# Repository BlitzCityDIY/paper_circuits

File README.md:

# paper_circuits
Repo for files used to create paper circuits with the Cricut

Cricut project link: https://design.cricut.com/landing/project-detail/5ef37191eb1aa703a4060cc2

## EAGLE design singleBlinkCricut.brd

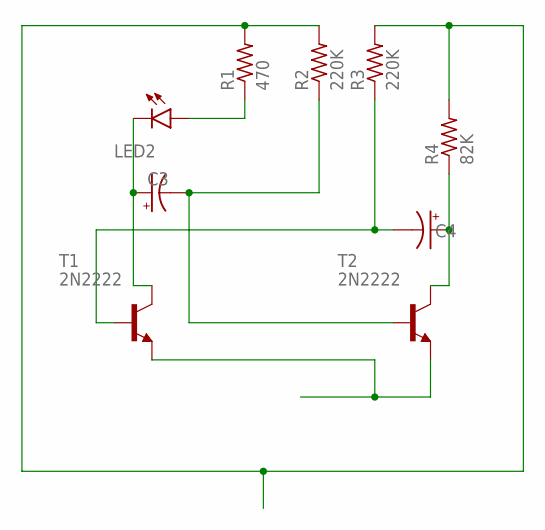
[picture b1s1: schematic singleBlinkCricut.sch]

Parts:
C3, C4: CPOL-USE2.5-6; E2,5-6
LED2: LED10MM
R1: 470; 0411/12
R2, R3: 220K; 0411/12
R4: 82K; 0411/12
T1, T2: 2N2222; TO92-EBC-OVAL

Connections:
3V: R1.2, R2.2, R3.2, R4.2
GND: T1.E, T2.E
unnamed: C3.-, R2.1, T2.B
unnamed: C3.+, LED2.K (C), T1.C
unnamed: LED2.A, R1.1
unnamed: C4.-, R3.1, T1.B
unnamed: C4.+, R4.1, T2.C

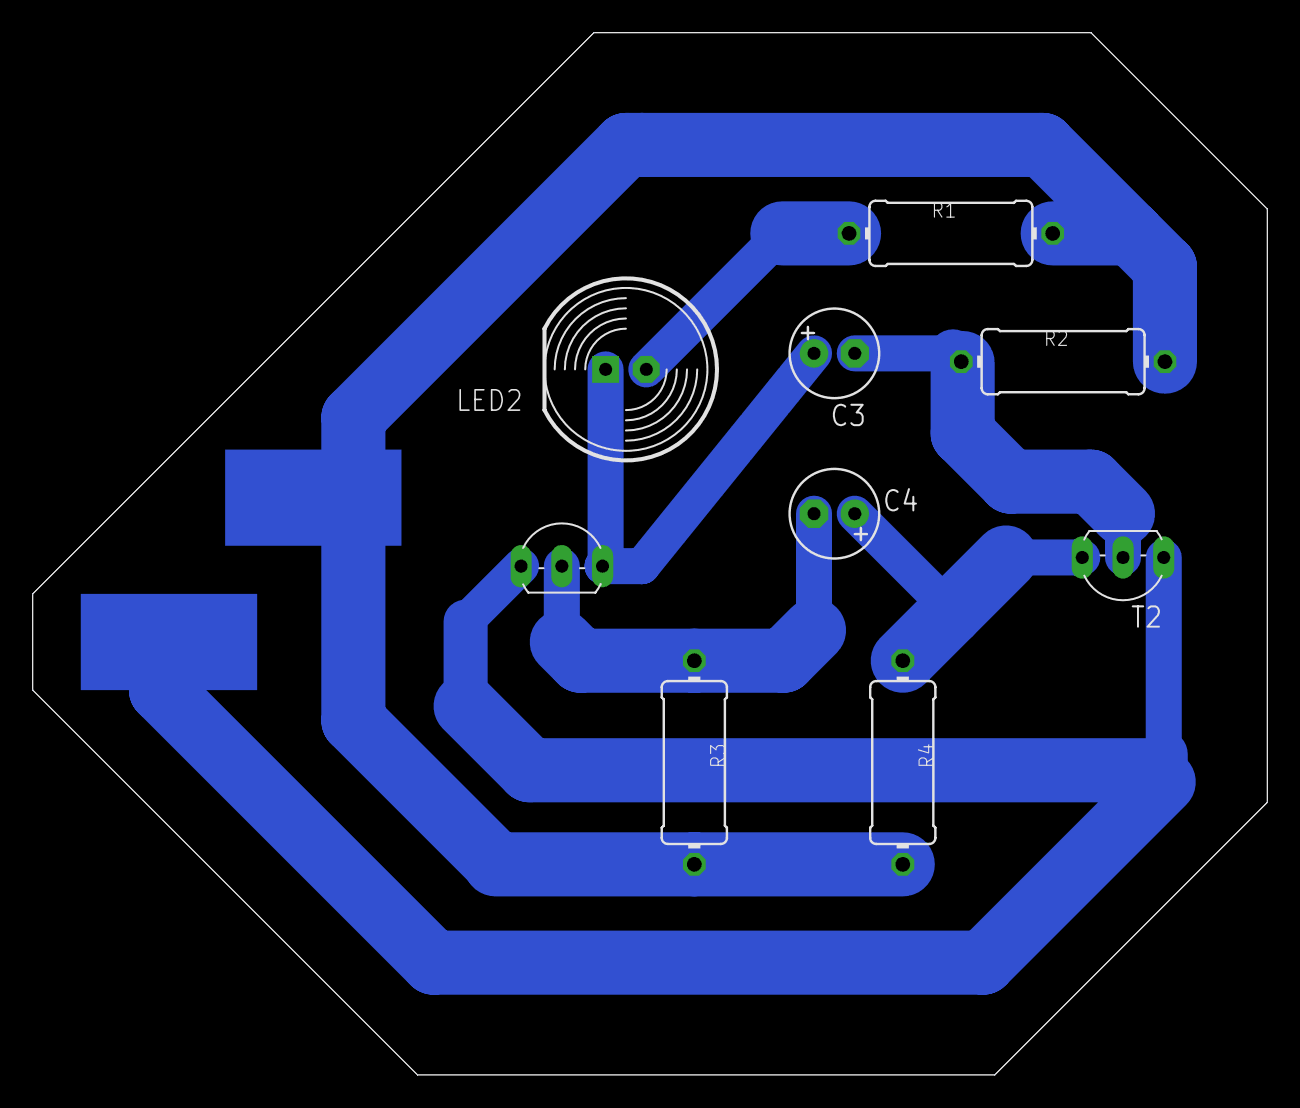
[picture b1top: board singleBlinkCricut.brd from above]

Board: 2 copper layers, 77.0 x 65.0 mm, 9 parts (0 on the bottom side), 7 nets.

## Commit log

2020-07-05 Adding files for circuit
    Eagle files, DXF and SVG files
2020-07-05 Update README.md
    adding cricut project link
